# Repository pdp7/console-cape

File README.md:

# console-cape
"psuedo" cape for the BeagleBone to display the serial console from the FTDI header on a TFT LCD.  The purpose is to be able to view U-Boot bootloader messages from the BeagleBone without having to have a laptop and USB-to-serial cable.

### Revision 1
* added header for [Adafruit 2.8" TFT LCD ILI9341 [PID 1770]](https://www.adafruit.com/product/1770)
* Commit: [c39be8a](https://github.com/pdp7/console-cape/commit/c39be8ada9da4000ea4db9afabc903f09d86c110)
* OSH Park shared project: [eaos4FIc](https://oshpark.com/projects/eaos4FIc)
* Date: 2017-08-25
* Bill of Materials
  * [Digi-key cart](http://www.digikey.com/short/31dhr0)
  * [Digi-key CSV files](https://raw.githubusercontent.com/pdp7/console-cape/master/bom/rev1/rev1-digikey-bom.csv)
  * note: more parts are in cart than are needed to build 1 board
* md5sum: d4032f9a1d718b31ddc5a06508fa7b02
* order: HVzmEK87

### Revision 0
* rough alpha prototype that is essentially just WickerLib ATMega328 breakout board with 16MHz crystal
* [Photos of prototype on Google+](https://plus.google.com/+DrewFustini/posts/R8djs28UbCG)
* Commit: [9690673](https://github.com/pdp7/wickerlib/commit/96906732c141e468960d03e7d56b61da5f02cf5b)
* OSH Park shared project: [CjWyM5EL](https://oshpark.com/shared_projects/CjWyM5EL)

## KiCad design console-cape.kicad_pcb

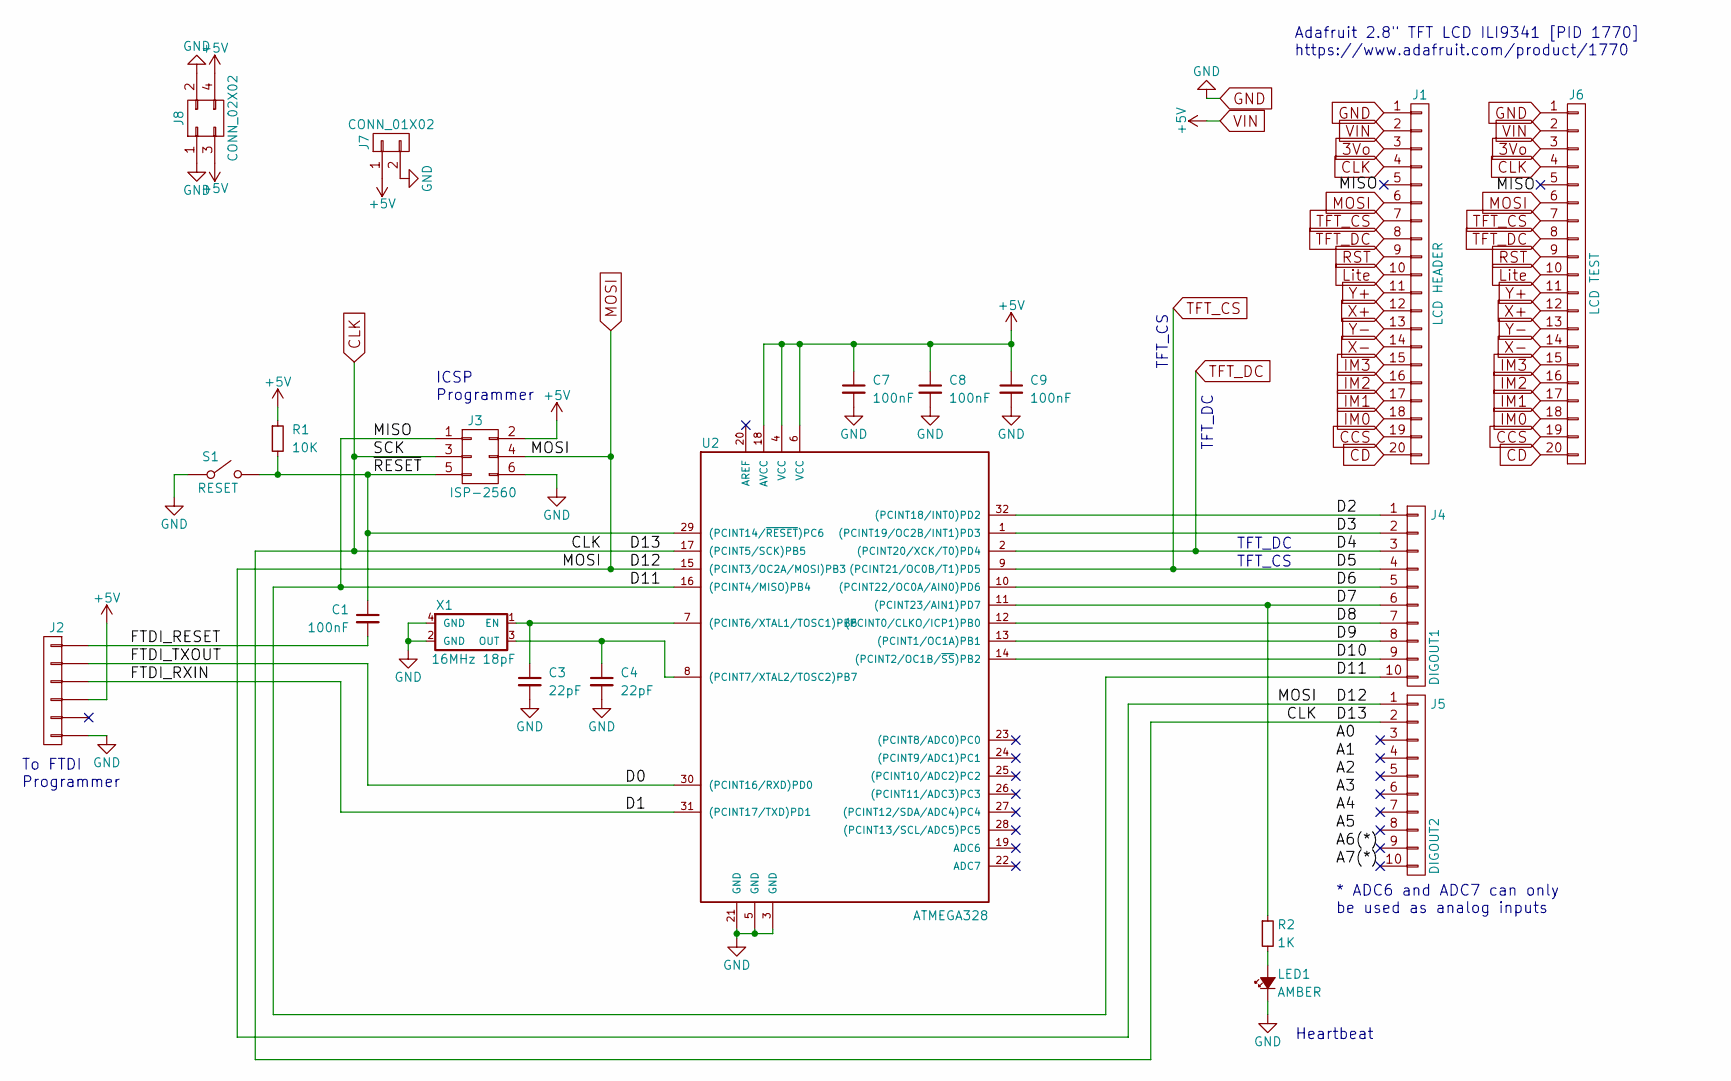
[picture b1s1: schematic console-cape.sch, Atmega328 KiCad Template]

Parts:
C1, C7, C8, C9: 100nF; RLC-0603-SMD
C3, C4: 22pF; RLC-0603-SMD
J1: LCD HEADER; CONN-HEADER-STRAIGHT-P2.54MM-1x20
J2: FTDI; CONN-HEADER-STRAIGHT-P2.54MM-1x06
J3: ISP-2560; CONN-HEADER-STRAIGHT-P2.54MM-2x03
J4: DIGOUT1; CONN-HEADER-STRAIGHT-P2.54MM-1x10
J5: DIGOUT2; CONN-HEADER-STRAIGHT-P2.54MM-1x10
J6: LCD TEST; CONN-HEADER-STRAIGHT-P2.54MM-1x20
J7: CONN_01X02; CONN-HEADER-STRAIGHT-P2.54MM-1x02
J8: CONN_02X02; CONN-HEADER-STRAIGHT-P2.54MM-2x02
LED1: AMBER; RLC-0603-SMD
R1: 10K; RLC-0805-SMD
R2: 1K; RLC-0603-SMD
S1: RESET; SWITCH-OMRON-MOMENTARY-SMD-B3U-1000P
U2: ATMEGA328; TQFP-32-7x7MM-P0.8MM
X1: 16MHz 18pF; CRYSTAL-CTS-4SMD

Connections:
3Vo: J1.3, J6.3
/D0: J2.2, U2.30 ((PCINT16/RXD)PD0)
/D1: J2.3, U2.31 ((PCINT17/TXD)PD1)
/D2: J4.1, U2.32 ((PCINT18/INT0)PD2)
/D3: J4.2, U2.1 ((PCINT19/OC2B/INT1)PD3)
/D6: J4.5, U2.10 ((PCINT22/OC0A/AIN0)PD6)
/D7: J4.6, R2.1, U2.11 ((PCINT23/AIN1)PD7)
/D8: J4.7, U2.12 ((PCINT0/CLKO/ICP1)PB0)
/D9: J4.8, U2.13 ((PCINT1/OC1A)PB1)
/D10: J4.9, U2.14 ((PCINT2/OC1B/~SS~)PB2)
/D11: J3.1, J4.10, U2.16 ((PCINT4/MISO)PB4)
/FTDI_RESET: C1.2, J2.1
/~RESET: C1.1, J3.5, R1.2, S1.2, U2.29 ((PCINT14/~RESET~)PC6)
CCS: J1.19, J6.19
CD: J1.20, J6.20
CLK: J1.4, J3.3, J5.2, J6.4, U2.17 ((PCINT5/SCK)PB5)
GND: C3.2, C4.2, C7.2, C8.2, C9.2, J1.1, J2.6, J3.6, J6.1, J7.2, J8.1, J8.2, LED1.1 (K), S1.1, U2.3 (GND), U2.5 (GND), U2.21 (GND), X1.2 (GND), X1.4 (GND); also elsewhere on the board
IM0: J1.18, J6.18
IM1: J1.17, J6.17
IM2: J1.16, J6.16
IM3: J1.15, J6.15
Lite: J1.10, J6.10
MOSI: J1.6, J3.4, J5.1, J6.6, U2.15 ((PCINT3/OC2A/MOSI)PB3)
unnamed: C3.1, U2.7 ((PCINT6/XTAL1/TOSC1)PB6), X1.1 (EN)
unnamed: C4.1, U2.8 ((PCINT7/XTAL2/TOSC2)PB7), X1.3 (OUT)
unnamed: LED1.2 (A), R2.2
RST: J1.9, J6.9
TFT_CS: J1.7, J4.4, J6.7, U2.9 ((PCINT21/OC0B/T1)PD5)
TFT_DC: J1.8, J4.3, J6.8, U2.2 ((PCINT20/XCK/T0)PD4)
VIN: C7.1, C8.1, C9.1, J1.2, J2.4, J3.2, J6.2, J7.1, J8.3, J8.4, R1.1, U2.4 (VCC), U2.6 (VCC), U2.18 (AVCC); also elsewhere on the board
X+: J1.12, J6.12
X-: J1.14, J6.14
Y+: J1.11, J6.11
Y-: J1.13, J6.13

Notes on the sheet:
To FTDI Programmer
ICSP Programmer
* ADC6 and ADC7 can only be used as analog inputs
Heartbeat
TFT_DC
TFT_CS
Adafruit 2.8" TFT LCD ILI9341 [PID 1770] https://www.adafruit.com/product/1770

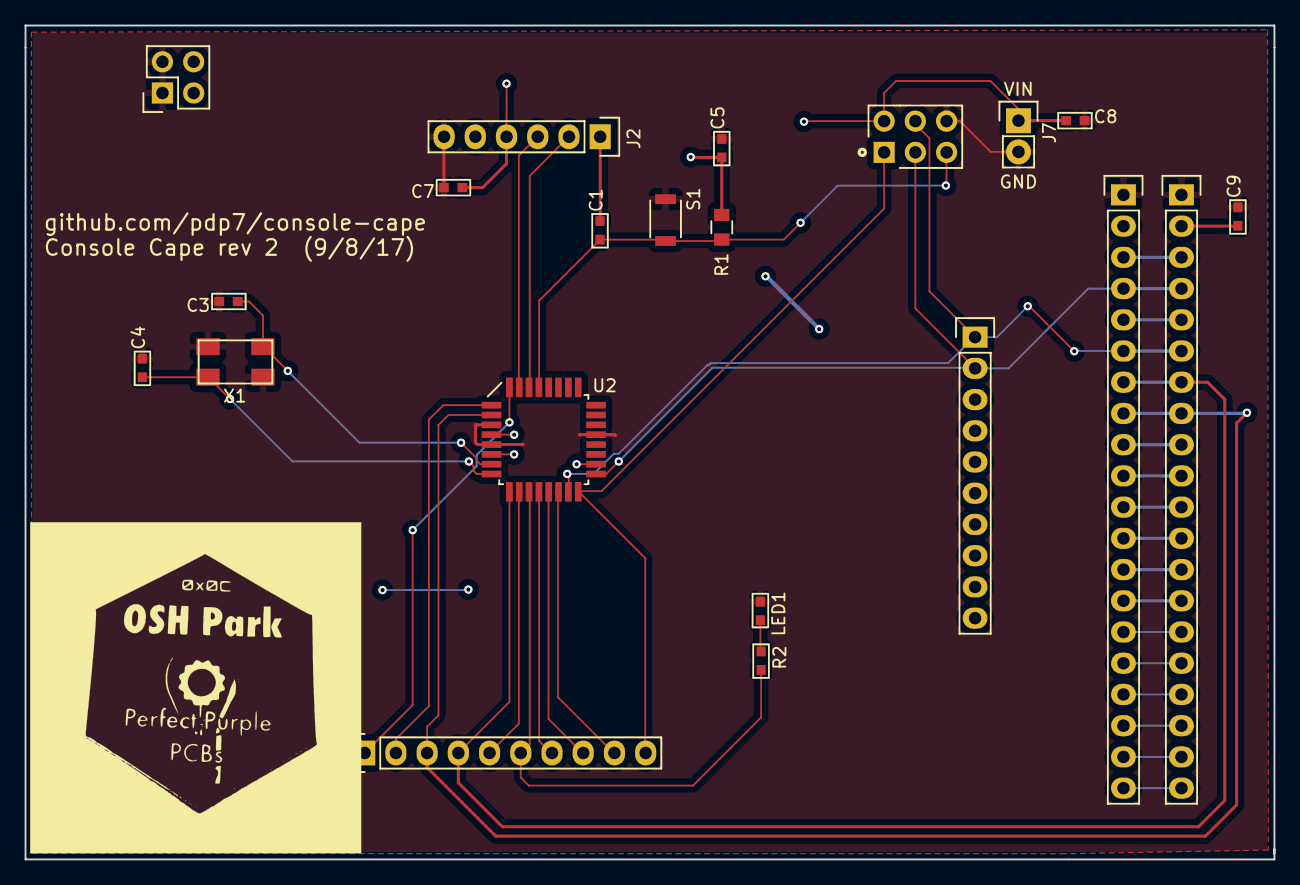
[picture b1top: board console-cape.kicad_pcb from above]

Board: 2 copper layers, 101.6 x 67.8 mm, 21 parts (0 on the bottom side), 34 nets.

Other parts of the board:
C5: 100nF; RLC-0603-SMD

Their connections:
GND: C5.2; also elsewhere on the board
VIN: C5.1; also elsewhere on the board

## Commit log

2017-08-26 add initial files
2017-08-26 clean up traces on top and bottom copper
2017-08-26 add gerbers to order stencil
2017-08-26 add project images for rev0 and rev1
2017-08-26 keep csv, xml and net files
2017-08-26 add rev1 digi-key bom
2017-08-26 create small version of images
2017-08-26 add shared project documentation and resize schematic
2017-08-26 update README link
2017-08-27 add Arduino test for Adafruit 3.5" LCD with HX8357
2017-08-28 add test code for HX8357
2017-09-08 added header to get GND and 3V3 from BBB P9
2017-09-08 add netlist

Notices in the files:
console-cape.kicad_pcb:
Released under the CERN Open Hardware License v1.2
